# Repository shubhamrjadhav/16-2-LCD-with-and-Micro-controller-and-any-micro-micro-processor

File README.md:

16-2-LCD-with-any-Micro-controller-and-any-micro-processor
Eagle Design for 16*2 LCD with any Micro controller and any micro micro processor

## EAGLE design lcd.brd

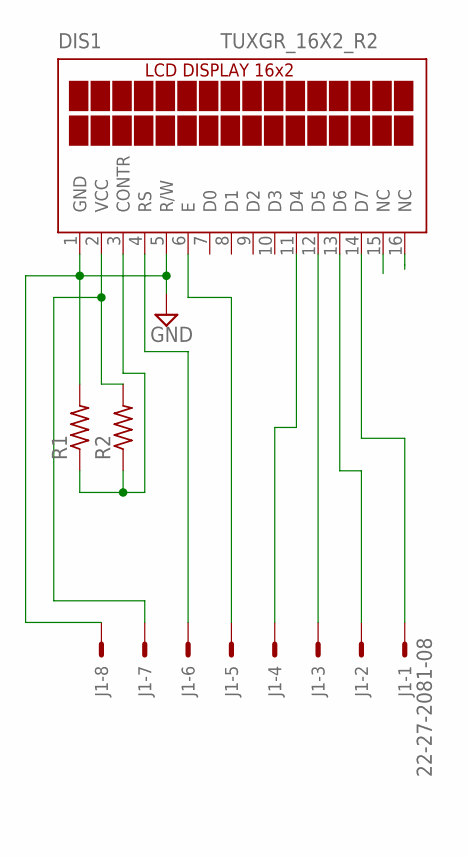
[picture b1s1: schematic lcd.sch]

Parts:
DIS1: TUXGR_16X2_R2
J1: 22-27-2081-08; 6410-08
R1, R2: R-US_0207/10; 0207/10

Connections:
GND: DIS1.1 (GND), DIS1.5 (R/W), DIS1.16 (NC), J1.8, R1.2
unnamed: DIS1.3 (CONTR), R1.1, R2.1
unnamed: DIS1.11 (D4), J1.4
unnamed: DIS1.12 (D5), J1.3
unnamed: DIS1.14 (D7), J1.1
unnamed: DIS1.13 (D6), J1.2
unnamed: DIS1.6 (E), J1.5
unnamed: DIS1.4 (RS), J1.6
VCC: DIS1.2 (VCC), DIS1.15 (NC), J1.7, R2.2

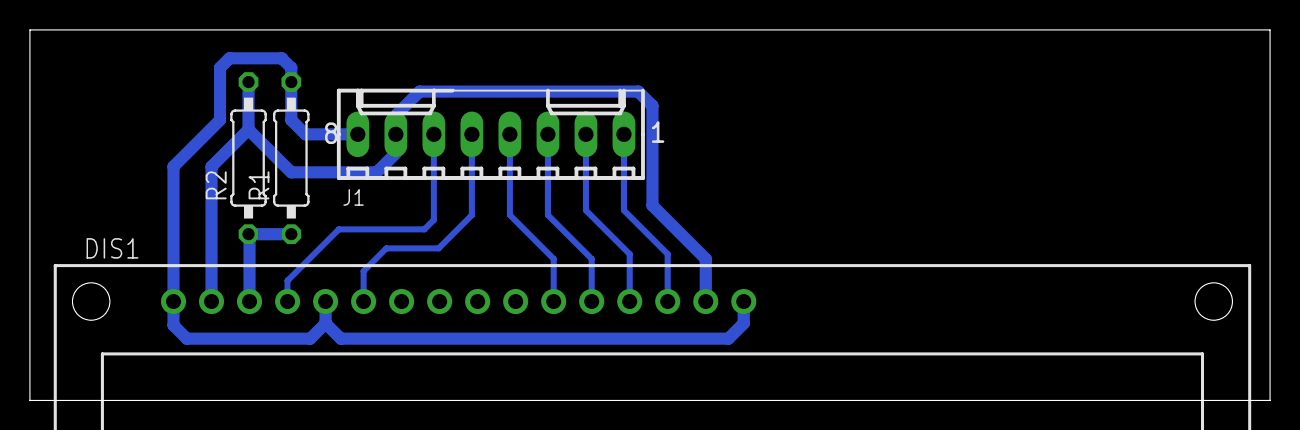
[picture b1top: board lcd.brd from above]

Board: 2 copper layers, 82.9 x 24.8 mm, 4 parts (0 on the bottom side), 9 nets.

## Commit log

2018-02-10 lcd 16*2
    use 4.7k resistor
